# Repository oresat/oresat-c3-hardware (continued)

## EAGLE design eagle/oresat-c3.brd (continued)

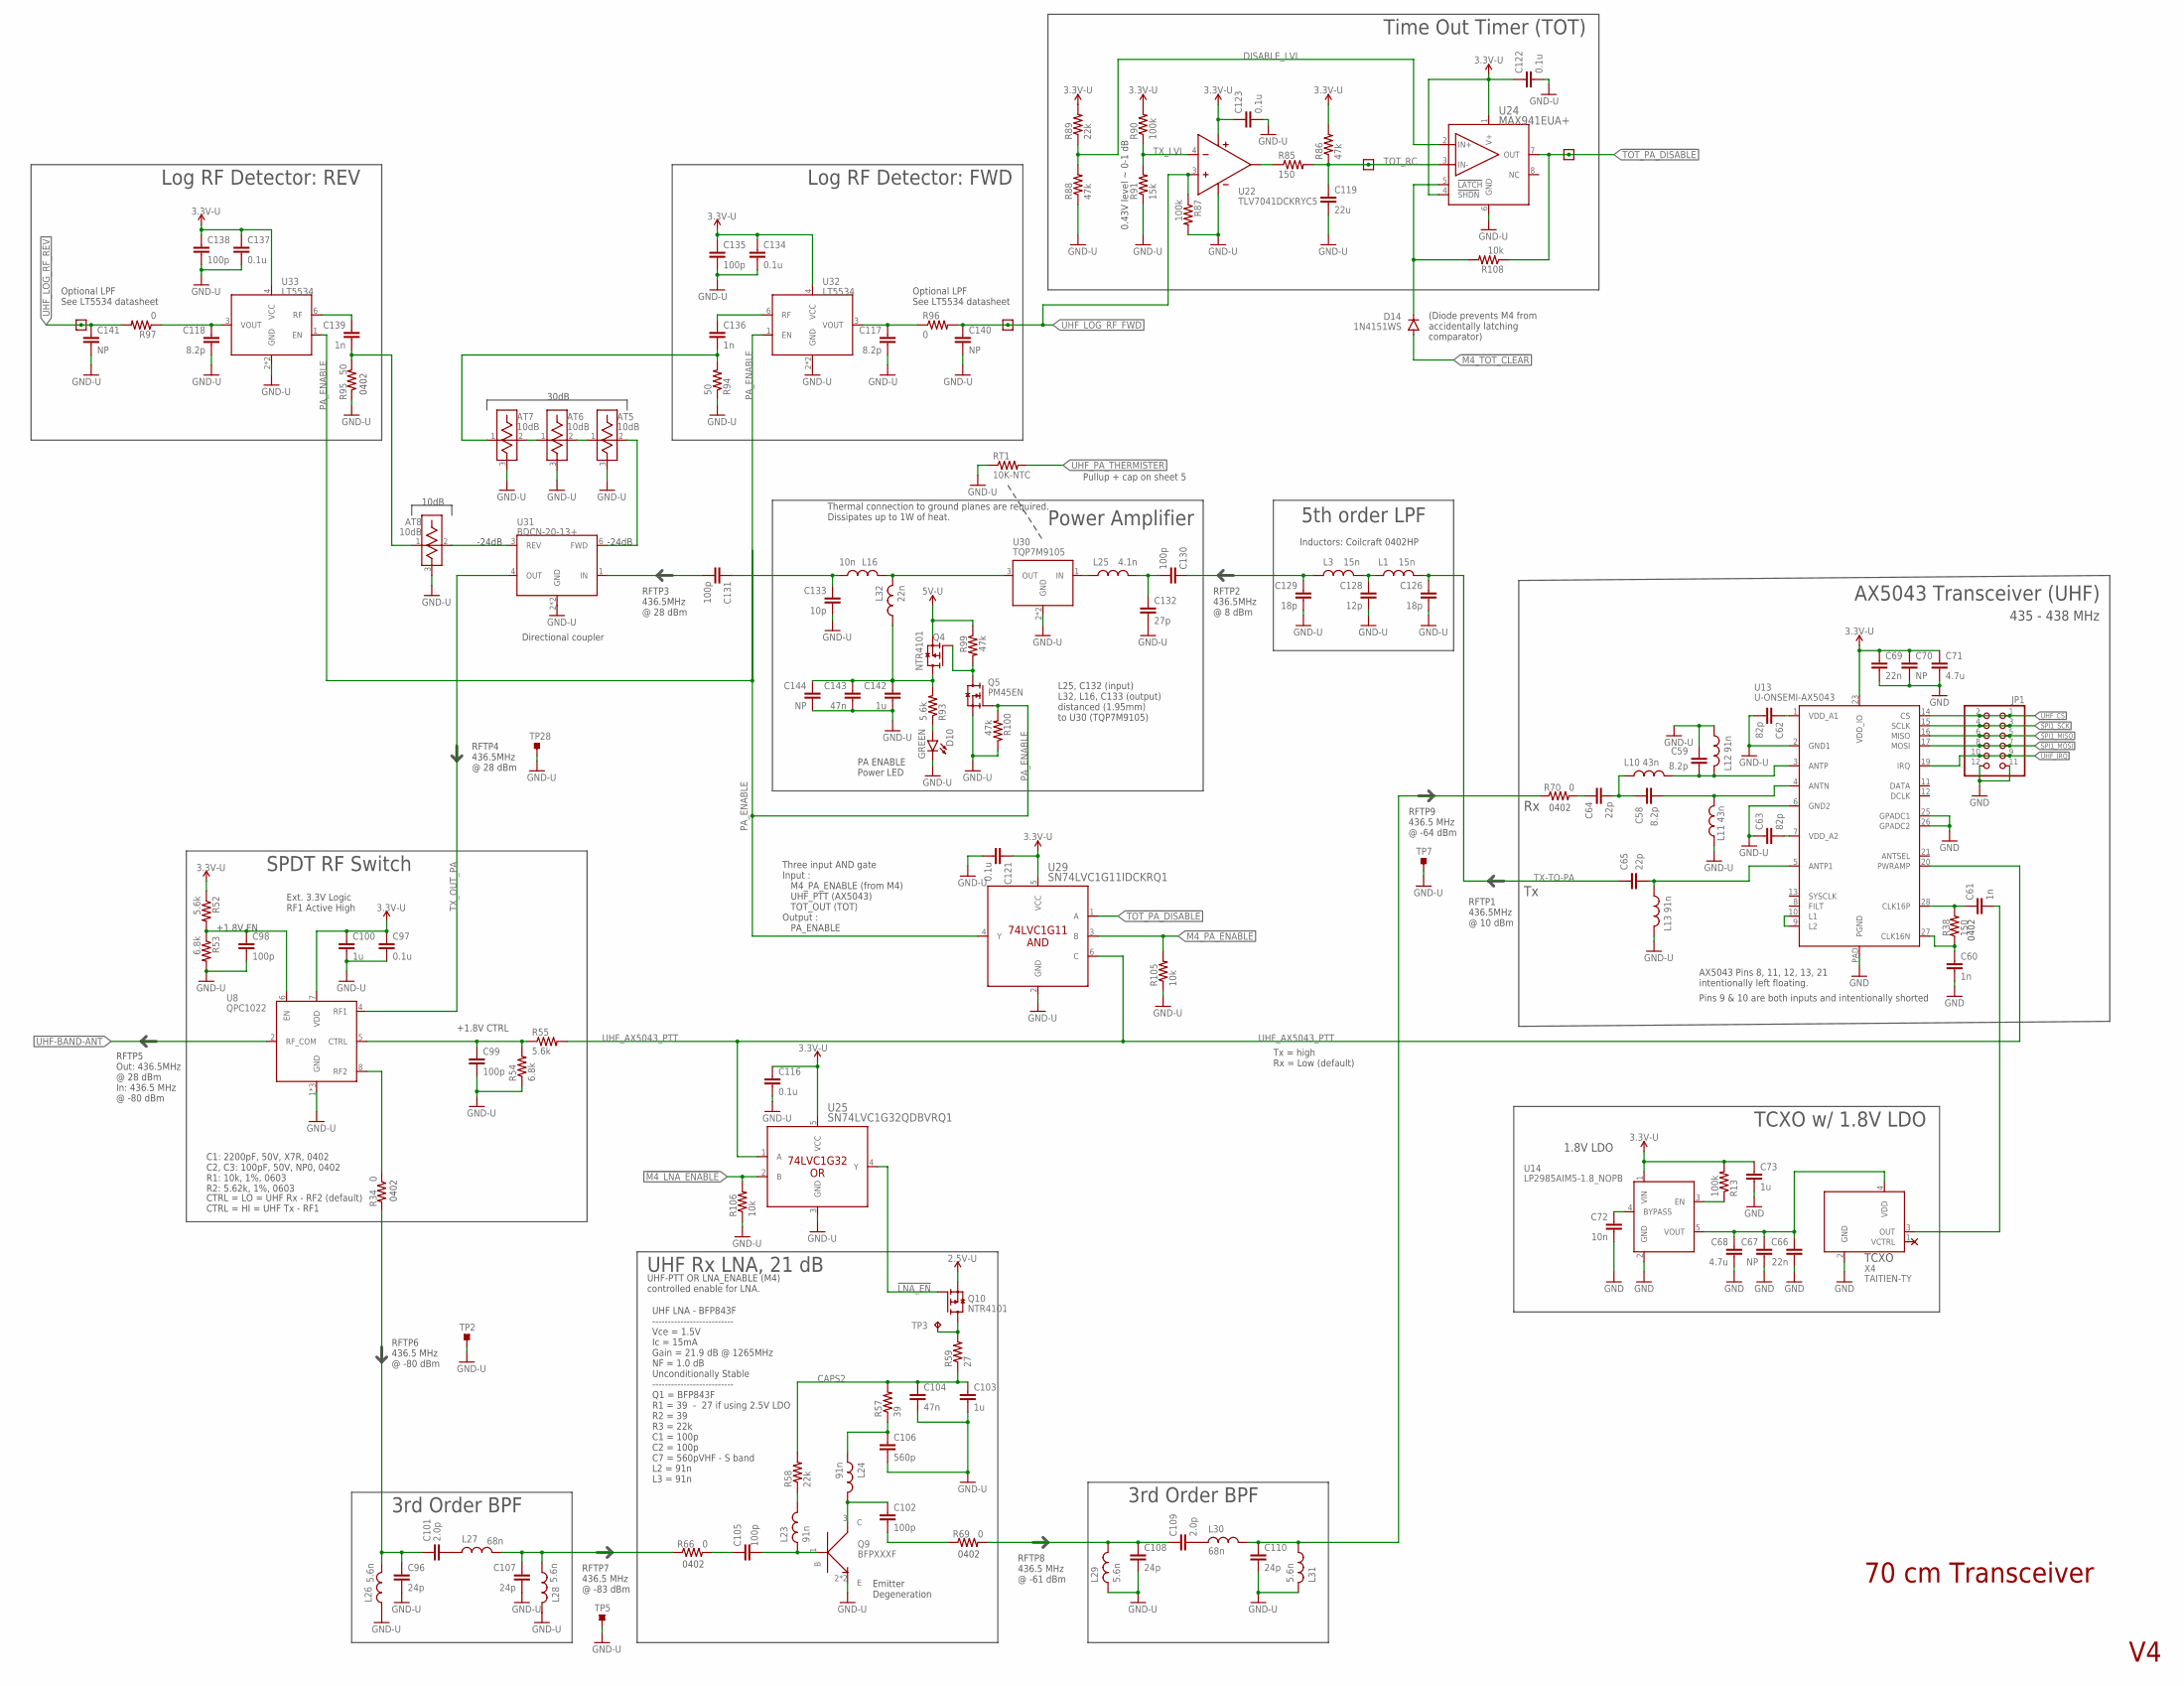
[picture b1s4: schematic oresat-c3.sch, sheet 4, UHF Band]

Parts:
AT5: 10dB; 0805
AT6, AT7, AT8: 10dB; 0603
C58, C59: 8.2p; .0402-C-NOSILK; MANUFACTURER_PART_NUMBER CL05C8R2CB5NNNC; DIGI-KEY_PART_NUMBER 1276-1729-1-ND
C60, C61: 1n; .0402-C-NOSILK; MANUFACTURER_PART_NUMBER CL05C102JB5NNNC; DIGI-KEY_PART_NUMBER 1276-1635-1-ND
C62, C63: 82p; .0402-C-NOSILK; MANUFACTURER_PART_NUMBER CL05C820JB5NNNC; DIGI-KEY_PART_NUMBER 1276-1726-1-ND
C64, C65: 22p; .0402-C-NOSILK; MANUFACTURER_PART_NUMBER CL05C220JB5NNNC; DIGI-KEY_PART_NUMBER 1276-1116-1-ND
C66, C69: 22n; .0603-C-NOSILK; MANUFACTURER_PART_NUMBER CL10B223KA8NNNC; DIGI-KEY_PART_NUMBER 1276-1999-1-ND
C67, C70, C140, C141, C144: NP; .0603-C-NOSILK
C68, C71: 4.7u; .0603-C-NOSILK; MANUFACTURER_PART_NUMBER CL10A475KO8NNNC; DIGI-KEY_PART_NUMBER 1276-1784-1-ND
C72: 10n; .0603-C-NOSILK; MANUFACTURER_PART_NUMBER CL10C103JA8NNNC; DIGI-KEY_PART_NUMBER 1276-2172-1-ND
C73, C100, C103: 1u; .0603-C-NOSILK; MANUFACTURER_PART_NUMBER CC0603KRX5R8BB105; DIGI-KEY_PART_NUMBER 311-1445-1-ND
C96, C107, C108, C110: 24p; .0402-C-NOSILK; MANUFACTURER_PART_NUMBER CL05C240JB5NNNC; DIGI-KEY_PART_NUMBER 1276-1670-1-ND
C97, C116, C121, C122, C123: 0.1u; .0603-C-NOSILK; MANUFACTURER_PART_NUMBER 0603ZD104KAT2A; DIGI-KEY_PART_NUMBER 478-0603ZD104KAT2ACT-ND
C98, C99: 100p; .0603-C-NOSILK; MANUFACTURER_PART_NUMBER 0603ZD104KAT2A; DIGI-KEY_PART_NUMBER 478-0603ZD104KAT2ACT-ND
C101, C109: 2.0p; .0402-C-NOSILK; MANUFACTURER_PART_NUMBER CC0402CRNPO9BN2R0; DIGI-KEY_PART_NUMBER 311-1006-2-ND
C102, C105: 100p; .0402-C-NOSILK; MANUFACTURER_PART_NUMBER CL05C102JB5NNNC; DIGI-KEY_PART_NUMBER 1276-1635-1-ND
C104: 47n; .0603-C-NOSILK; MANUFACTURER_PART_NUMBER CL10B473KB8NNNC; DIGI-KEY_PART_NUMBER 1276-1063-1-ND
C106: 560p; .0402-C-NOSILK; MANUFACTURER_PART_NUMBER CL05C561JB5NNNC; DIGI-KEY_PART_NUMBER 1276-1709-1-ND
C117, C118: 8.2p; .0603-C-NOSILK
C119: 22u; .0603-C-NOSILK
C126, C129: 18p; .0402-C-NOSILK; MANUFACTURER_PART_NUMBER CL05C180JB5NNNC; DIGI-KEY_PART_NUMBER 1276-1140-1-ND
C128: 12p; .0402-C-NOSILK; MANUFACTURER_PART_NUMBER CL05C120JB5NNNC; DIGI-KEY_PART_NUMBER 1276-1178-1-ND
C130: 100p; .0402-C-NOSILK
C131, C135, C138: 100p; .0603-C-NOSILK
C132: 27p; .0402-C-NOSILK
C133: 10p; .0603-C-NOSILK
C134, C137: 0.1u; .0603-C-NOSILK
C136, C139: 1n; .0402-C-NOSILK
C142: 1u; .0603-C-NOSILK
C143: 47n; .0603-C-NOSILK
D10: GREEN; LED-0603
D14: 1N4151WS; SOD323-R
JP1: PINHD-2X6; 2X06; MANUFACTURER_PART_NUMBER 61301221121; DIGI-KEY_PART_NUMBER 732-5297-ND
L1, L3: 15n; .0402-C-NOSILK; MANUFACTURER_PART_NUMBER 0402HP-15NXGLW; DIGI-KEY_PART_NUMBER 2035-1081-1-ND
L10, L11: 43n; .0402-C-NOSILK; MANUFACTURER_PART_NUMBER LQW15AN43NG8ZD; DIGI-KEY_PART_NUMBER 490-15447-1-ND
L12, L13, L23, L24: 91n; .0603-C-NOSILK; MANUFACTURER_PART_NUMBER LQW18AN91NG8ZD; DIGI-KEY_PART_NUMBER 490-15756-1-ND
L16: 10n; .0603-C-NOSILK
L25: 4.1n; .0402-C-NOSILK
L26, L28, L29, L31: 5.6n; .0402-C-NOSILK; MANUFACTURER_PART_NUMBER 0402HP-5N6XGLW; MOUSER_PART_NUMBER 994-0402HP-5N6XGLW
L27, L30: 68n; .0402-C-NOSILK; MANUFACTURER_PART_NUMBER 0402HPH-68NXGLW; MOUSER_PART_NUMBER 994-0402HPH-68NXGLW
L32: 22n; .0805-C-NOSILK
Q4: NTR4101; SOT23-3
Q5: PM45EN; SOT23-3
Q9: BFPXXXF; TSFP4; MANUFACTURER_PART_NUMBER BFP740FH6327XTSA1; DIGI-KEY_PART_NUMBER BFP740FH6327XTSA1CT-ND
Q10: NTR4101; SOT23-3; MANUFACTURER_PART_NUMBER BSS84; DIGI-KEY_PART_NUMBER BSS84CT-ND
R13, R87, R90: 100k; .0603-C-NOSILK
R34, R66, R69, R70: 0; .0402-C-NOSILK; MANUFACTURER_PART_NUMBER RMCF0402ZT0R00; DIGI-KEY_PART_NUMBER RMCF0402ZT0R00CT-ND
R38: 150; .0402-C-NOSILK; MANUFACTURER_PART_NUMBER RT0402BRD07150RL; DIGI-KEY_PART_NUMBER YAG4175CT-ND
R52, R55, R93: 5.6k; .0603-C-NOSILK
R53, R54: 6.8k; .0603-C-NOSILK
R57: 39; .0603-C-NOSILK; MANUFACTURER_PART_NUMBER RMCF0603FT39R0; DIGI-KEY_PART_NUMBER RMCF0603FT39R0CT-ND
R58: 22k; .0603-C-NOSILK; MANUFACTURER_PART_NUMBER ERJ-3EKF2202V; DIGI-KEY_PART_NUMBER P22.0KHCT-ND
R59: 27; .0603-C-NOSILK; MANUFACTURER_PART_NUMBER RMCF0603FT27R0; DIGI-KEY_PART_NUMBER RMCF0603FT27R0CT-ND
R85: 150; .0603-C-NOSILK
R86, R88, R99, R100: 47k; .0603-C-NOSILK
R89: 22k; .0603-C-NOSILK
R91: 15k; .0603-C-NOSILK
R94, R95: 50; .0402-C-NOSILK
R96, R97: 0; .0603-C-NOSILK
R105, R106, R108: 10k; .0603-C-NOSILK
RT1: 10K-NTC; .0603-C-NOSILK
TP1, TP6, TP10, TP29: TEST-POINT-LARGE-SQUARE; 1X01
TP2, TP5, TP7, TP28: TEST-POINT_SMD-SMD-10SN; TESTPOINT_SMD-10SN
TP3: TEST-POINT-LARGE; 1X01
TP4: NO-CONNECTNO-CONNECT-DEVICE; NO-CONNECT-FOOTPRINT
U8: QPC1022; MANUFACTURER_PART_NUMBER QPC1022TR7; MOUSER_PART_NUMBER 772-QPC1022TR7
U13: U-ONSEMI-AX5043; QFN28-5X5-WITH-CENTER-PAD; MANUFACTURER_PART_NUMBER AX5043-1-TW30; DIGI-KEY_PART_NUMBER AX5043-1-TW30OSCT-ND
U14: LP2985AIM5-1.8_NOPB; SOT-23; DIGI-KEY_PART_NUMBER LP2985AIM5-1.8/NOPBCT-ND
U22: TLV7041DCKRYC5; SC70-5
U24: MAX941EUA+; 21-0036K_MXM
U25: SN74LVC1G32QDBVRQ1; DBV5
U29: SN74LVC1G11IDCKRQ1; DCK6
U30: TQP7M9105; U-QORVO-TQP7M9105-PA_TQP7M9105
U31: BDCN-20-13+
U32, U33: LT5534; SC70
X4: TAITIEN-TY; 2.5X2.0; MANUFACTURER_PART_NUMBER TYKTBLSANF-16.000000; DIGI-KEY_PART_NUMBER 1664-1323-1-ND

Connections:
1.8V-U: C66.1, C67.1, C68.1, U14.5 (VOUT), X4.4 (VDD)
2.5V-U: Q10.2 (S); also elsewhere on the board
3.3V-U: C69.1, C70.1, C71.1, C73.1, C97.1, C100.1, C116.1, C121.1, C122.1, C123.1, C134.1, C135.1, C137.1, C138.1, R13.2, R52.1, R86.2, R89.2, R90.2, U8.7 (VDD), U13.23 (VDD_IO), U14.1 (VIN), U22.5 (VCC), U24.1 (V+), U24.4 (!SHDN), U25.5 (VCC), U29.5 (VCC), U32.4 (VCC), U33.4 (VCC); also elsewhere on the board
5V-U: Q4.2 (S), R99.1; also elsewhere on the board
!LATCH_FEEDBACK: D14.C, R108.2, U24.5 (!LATCH)
!LNA_EN: Q10.1 (G), U25.4 (Y)
!M4_LNA_ENABLE: R106.2, U25.2 (B); also elsewhere on the board
!M4_TOT_CLEAR: D14.A; also elsewhere on the board
!TOT_PA_DISABLE: R108.1, TP1.1, U24.7 (OUT), U29.1 (A); also elsewhere on the board
ANTN2: C58.2, L11.2, U13.4 (ANTN)
ANTP4: C59.2, L10.2, L12.1, U13.3 (ANTP)
ANTP5: C65.2, L13.2, U13.5 (ANTP1)
B2: C105.2, L23.1, Q9.1 (B)
C2: C102.1, L24.2, Q9.3 (C)
CAPS2: C103.1, C104.1, R57.2, R58.2, R59.1
CAPS3: C142.1, C143.1, C144.1, L32.2, Q4.3 (D), R93.2
CLKN2: C60.1, R38.1, U13.27 (CLK16N)
CLKP2: C61.1, R38.2, U13.28 (CLK16P)
CTRL1: C99.1, R54.2, R55.1, U8.5 (CTRL)
DISABLE_LVL: R88.2, R89.1, U24.2 (IN+)
EN1: C98.1, R52.2, R53.1, U8.6 (EN)
GND: C60.2, C66.2, C67.2, C68.2, C69.2, C70.2, C71.2, C72.2, C73.2, JP1.11, JP1.12, U13.25 (GPADC1), U13.26 (GPADC2), U13.PAD (PGND), U14.2 (GND), X4.2 (GND); also elsewhere on the board
GND-U: AT5.3 (GND), AT6.3 (GND), AT7.3 (GND), AT8.3 (GND), C59.1, C62.2, C63.1, C96.2, C97.2, C98.2, C99.2, C100.2, C103.2, C104.2, C106.2, C107.2, C108.2, C110.2, C116.2, C117.2, C118.2, C119.2, C121.2, C122.2, C123.2, C126.2, C128.2, C129.2, C132.2, C133.2, C134.2, C135.2, C137.2, C138.2, C140.2, C141.2, C142.2, C143.2, C144.2, D10.C, L11.1, L12.2, L13.1, L26.1, L28.1, L29.1, L31.1, Q5.2 (S), Q9.2 (E), Q9.4 (E), R53.2, R54.1, R87.2, R88.1, R91.1, R94.1, R95.1, R100.1, R105.1, R106.1, RT1.1, TP2.TP, TP5.TP, TP7.TP, TP28.TP, U8.1 (GND), U8.3 (GND), U8.9 (GND), U13.2 (GND1), U13.6 (GND2), U22.2 (VEE), U24.6 (GND), U25.3 (GND), U29.2 (GND), U30.2 (GND), U30.PAD (GND), U31.2 (GND), U31.5 (GND), U32.2 (GND), U32.5 (GND), U33.2 (GND), U33.5 (GND); also elsewhere on the board
M4_PA_ENABLE: R105.2, U29.3 (B); also elsewhere on the board
unnamed: AT5.1, AT6.2
unnamed: C61.2, X4.3 (OUT)
unnamed: C117.1, R96.1, U32.3 (VOUT)
unnamed: U13.9 (L2), U13.10 (L1)
unnamed: C62.1, U13.1 (VDD_A1)
unnamed: C63.2, U13.7 (VDD_A2)
unnamed: C58.1, C64.2, L10.1
unnamed: AT6.1, AT7.2
unnamed: C101.2, L27.1
unnamed: R13.1, U14.3 (EN)
unnamed: L23.2, R58.1
unnamed: C106.1, L24.1, R57.1
unnamed: C72.1, U14.4 (BYPASS)
unnamed: C109.2, L30.1
unnamed: Q10.3 (D), R59.2, TP3.1
unnamed: R34.1, U8.8 (RF2)
unnamed: C105.1, R66.2
unnamed: C102.2, R69.1
unnamed: C64.1, R70.2
unnamed: C118.1, R97.1, U33.3 (VOUT)
unnamed: C128.1, L1.2, L3.1
unnamed: C129.1, C130.1, L3.2
unnamed: R85.1, U22.1 (OUT)
unnamed: C136.1, U32.6 (RF)
unnamed: AT7.1, C136.2, R94.2
unnamed: C139.1, U33.6 (RF)
unnamed: AT8.1, C139.2, R95.2
unnamed: AT5.2, U31.6 (FWD)
unnamed: AT8.2, U31.3 (REV)
unnamed: Q4.1 (G), Q5.3 (D), R99.2
unnamed: D10.A, R93.1
PA_ENABLE: Q5.1 (G), R100.2, U29.4 (Y), U32.1 (EN), U33.1 (EN)
RX2: C110.1, L30.2, L31.2, R70.1
SPI1_MISO: JP1.5, JP1.6, U13.16 (MISO); also elsewhere on the board
SPI1_MOSI: JP1.7, JP1.8, U13.17 (MOSI); also elsewhere on the board
SPI1_SCK: JP1.3, JP1.4, U13.15 (SCLK); also elsewhere on the board
TOT_RC: C119.1, R85.2, R86.1, TP6.1, U24.3 (IN-)
TX-TO-PA: C65.1, C126.1, L1.1
TX-TO-PA$1: C130.2, C132.1, L25.1
TX-TO-PA$2: L25.2, U30.1 (IN)
TX_LVL: R90.1, R91.2, U22.4 (IN-)
TX_OUT: L16.1, L32.1, U30.3 (OUT)
TX_OUT_PA: U8.4 (RF1), U31.4 (OUT)
TX_OUT_PA$1: C131.2, U31.1 (IN)
TX_OUT_PA$2: C131.1, C133.1, L16.2
U-BFP-LNA-RF_IN: C107.1, L27.2, L28.2, R66.1
U-BFP-LNA-RF_OUT: C108.1, C109.1, L29.2, R69.2
UHF-BAND-ANT: U8.2 (RF_COM); also elsewhere on the board
UHF-RX: C96.1, C101.1, L26.2, R34.2
UHF_AX5043_PTT: R55.2, U13.20 (PWRAMP), U25.1 (A), U29.6 (C)
UHF_CS: JP1.1, JP1.2, U13.14 (CS); also elsewhere on the board
UHF_IRQ: JP1.9, JP1.10, U13.19 (IRQ); also elsewhere on the board
UHF_LOG_RF_FWD: C140.1, R87.1, R96.2, TP10.1, U22.3 (IN+); also elsewhere on the board
UHF_LOG_RF_REV: C141.1, R97.2, TP29.1; also elsewhere on the board
UHF_PA_THERMISTER: RT1.2; also elsewhere on the board

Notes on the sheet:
70 cm Transceiver
435 - 438 MHz
AX5043 Pins 8, 11, 12, 13, 21 intentionally left floating.
1.8V LDO
TCXO w/ 1.8V LDO
TCXO
C1: 2200pF, 50V, X7R, 0402 C2, C3: 100pF, 50V, NP0, 0402 R1: 10k, 1%, 0603 R2: 5.62k, 1%, 0603
+1.8V EN
Ext. 3.3V Logic RF1 Active High
+1.8V CTRL
UHF LNA - BFP843F -------------------------- Vce = 1.5V Ic = 15mA Gain = 21.9 dB @ 1265MHz NF = 1.0 dB Unconditionally Stable -------------------------- Q1 = BFP843F R1 = 39 - 27 if using 2.5V LDO R2 = 39 R3 = 22k C1 = 100p C2 = 100p C7 = 560pVHF - S band L2 = 91n L3 = 91n
Emitter Degeneration
3rd Order BPF
AX5043 Transceiver (UHF)
UHF Rx LNA, 21 dB
SPDT RF Switch
CTRL = LO = UHF Rx - RF2 (default) CTRL = HI = UHF Tx - RF1
UHF-PTT OR LNA_ENABLE (M4) controlled enable for LNA.
Pins 9 & 10 are both inputs and intentionally shorted
Power Amplifier
-24dB
Optional LPF See LT5534 datasheet
Thermal connection to ground planes are required. Dissipates up to 1W of heat.
L25, C132 (input) L32, L16, C133 (output) distanced (1.95mm) to U30 (TQP7M9105)
30dB
10dB
Three input AND gate Input : M4_PA_ENABLE (from M4) UHF_PTT (AX5043) TOT_OUT (TOT) Output : PA_ENABLE
PA ENABLE Power LED
(Diode prevents M4 from accidentally latching comparator)
Tx = high Rx = Low (default)
Log RF Detector: FWD
Log RF Detector: REV
Time Out Timer (TOT)
Directional coupler
Pullup + cap on sheet 5
5th order LPF
Inductors: Coilcraft 0402HP
0402
0.43V level ~ 0-1 dB
RFTP1 436.5MHz @ 10 dBm

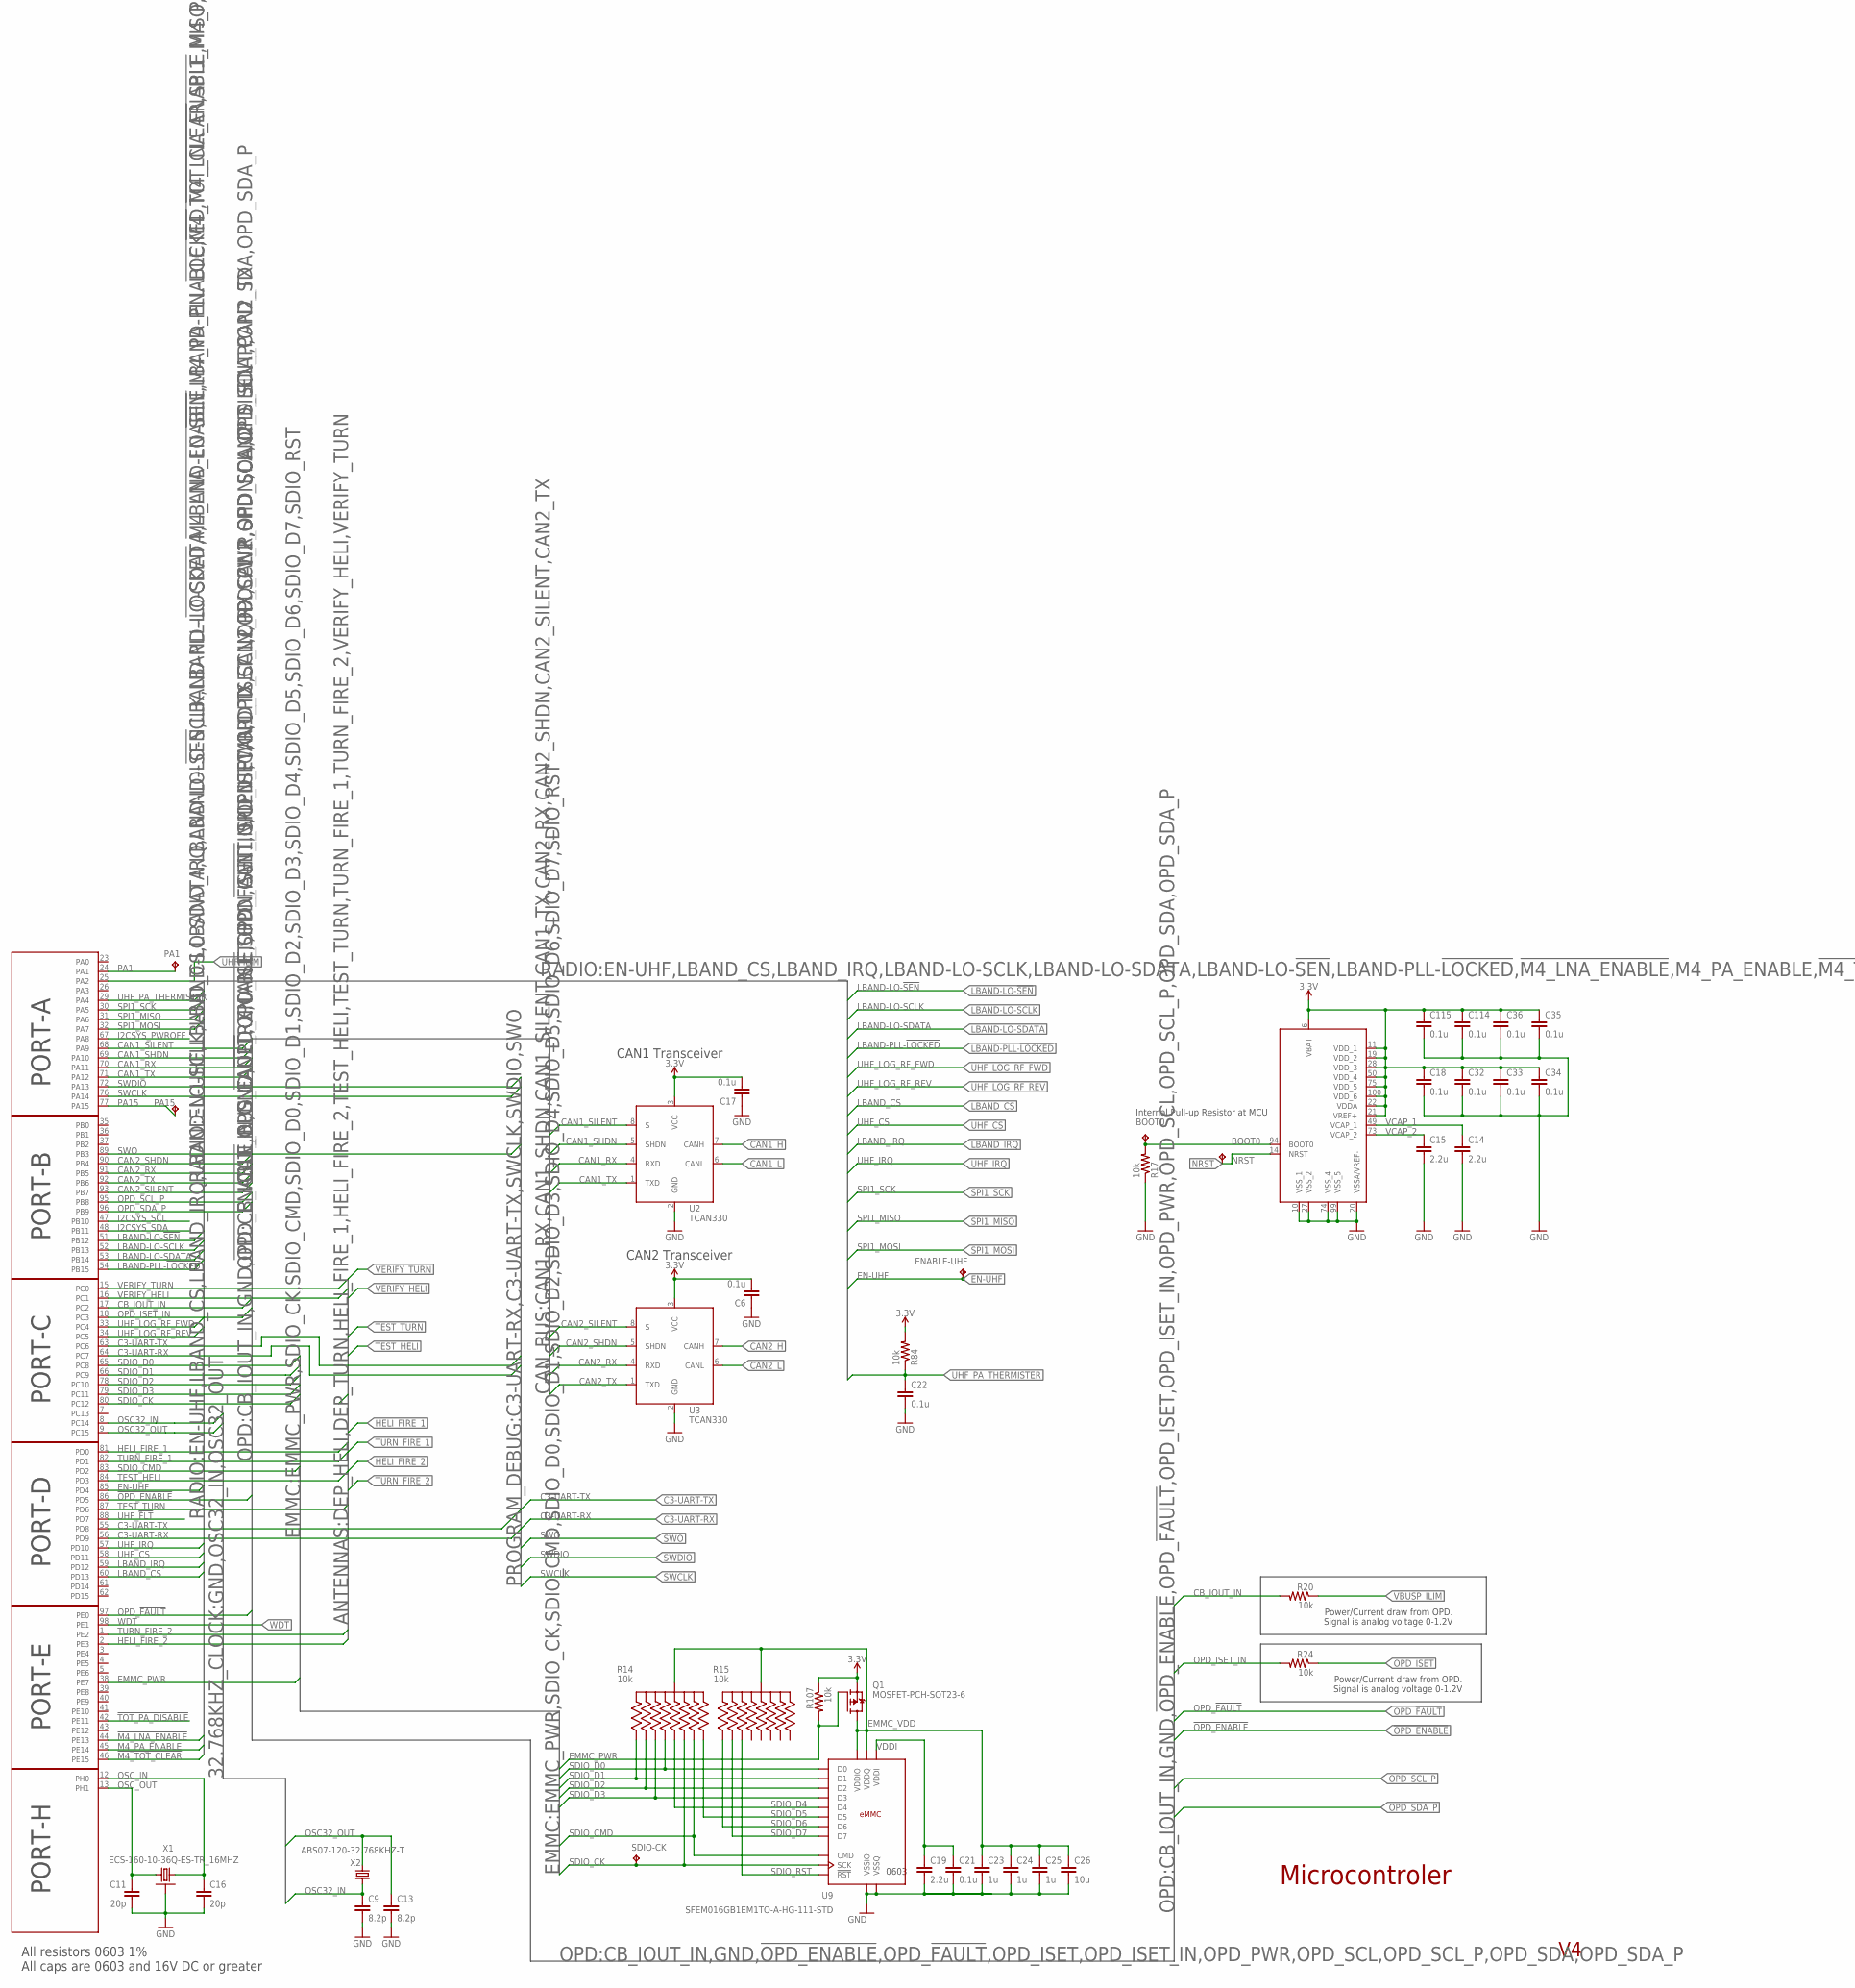
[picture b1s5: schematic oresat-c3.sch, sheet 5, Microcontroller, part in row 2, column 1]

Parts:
BOOT0: TEST-POINT-LARGE; 1X01
C6, C17, C18, C21, C22, C32, C33, C34, C35, C36, C114, C115: 0.1u; .0603-C-NOSILK
C9, C13: 8.2p; .0603-C-NOSILK
C11, C16: 20p; .0603-C-NOSILK
C14, C15, C19: 2.2u; .0603-C-NOSILK
C23, C24, C25: 1u; .0603-C-NOSILK
C26: 10u; .0603-C-NOSILK
ENABLE-UHF: TEST-POINT-LARGE; 1X01
NRST: TEST-POINT-LARGE; 1X01
PA1, PA15: TEST-POINT-LARGE; 1X01
Q1: MOSFET-PCH-SOT23-6; SOT23-6; MANUFACTURER_PART_NUMBER DMP3050LVT-7; DIGI-KEY_PART_NUMBER DMP3050LVT-7DICT-ND
R14, R15: 10k; ARRAY_EXBA-M; DIGI-KEY_PART_NUMBER U7103CT-ND
R17, R20, R24, R84, R107: 10k; .0603-C-NOSILK
SDIO-CK: TEST-POINT-LARGE; 1X01
U2, U3: TCAN330; SOT23-8_TI-DCN; MANUFACTURER_PART_NUMBER TCAN330GDCNT; DIGI-KEY_PART_NUMBER 296-44211-1-ND
U9: SFEM016GB1EM1TO-A-HG-111-STD; BGA-153(11.5X13)(EMMC-BA); MANUFACTURER_PART_NUMBER SFEM016GB1EA1TO-I-GE-111-STD; MOUSER_PART_NUMBER 922-500530
U36: STM32F439VIT6_PORT_BREAKOUT; QFP50P1600X1600X160-100N
X1: ECS-160-10-36Q-ES-TR_16MHZ; 2.5X2.0
X2: ABS07-120-32.768KHZ-T; ABS07-32.768KHZ-T

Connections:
3.3V: C6.2, C17.2, C18.1, C32.1, C33.1, C34.1, C35.1, C36.1, C114.1, C115.1, Q1.4 (S), R84.2, R107.1, U2.3 (VCC), U3.3 (VCC), U36.6 (VBAT), U36.11 (VDD_1), U36.19 (VDD_2), U36.21 (VREF+), U36.22 (VDDA), U36.28 (VDD_3), U36.50 (VDD_4), U36.75 (VDD_5), U36.100 (VDD_6); also elsewhere on the board
!M4_LNA_ENABLE: U36.44 (PE13); also elsewhere on the board
!M4_TOT_CLEAR: U36.46 (PE15); also elsewhere on the board
!OPD_ENABLE: U36.86 (PD5); also elsewhere on the board
!TOT_PA_DISABLE: U36.42 (PE11); also elsewhere on the board
BOOT0: BOOT0.1, R17.2, U36.94 (BOOT0)
C3-UART-RX: U36.56 (PD9), U36.64 (PC7); also elsewhere on the board
C3-UART-TX: U36.55 (PD8), U36.63 (PC6); also elsewhere on the board
CAN1_H: U2.7 (CANH); also elsewhere on the board
CAN1_L: U2.6 (CANL); also elsewhere on the board
CAN1_RX: U2.4 (RXD), U36.70 (PA11)
CAN1_SHDN: U2.5 (SHDN), U36.69 (PA10)
CAN1_SILENT: U2.8 (S), U36.68 (PA9)
CAN1_TX: U2.1 (TXD), U36.71 (PA12)
CAN2_H: U3.7 (CANH); also elsewhere on the board
CAN2_L: U3.6 (CANL); also elsewhere on the board
CAN2_RX: U3.4 (RXD), U36.91 (PB5)
CAN2_SHDN: U3.5 (SHDN), U36.90 (PB4)
CAN2_SILENT: U3.8 (S), U36.93 (PB7)
CAN2_TX: U3.1 (TXD), U36.92 (PB6)
CB_IOUT_IN: R20.2, U36.17 (PC2)
EMMC_PWR: Q1.3 (G), R107.2, U36.38 (PE7)
EMMC_VDD: C23.1, C24.1, C25.1, C26.1, Q1.1 (D), Q1.2 (D), Q1.5 (D), Q1.6 (D), R14.5 (55), R14.10 (55), R15.5 (55), R15.10 (55), U9.C6 (VDDQ), U9.E6 (VDDIO), U9.F5 (VDDIO), U9.J10 (VDDIO), U9.K9 (VDDIO), U9.M4 (VDDQ), U9.N4 (VDDQ), U9.P3 (VDDQ), U9.P5 (VDDQ), U9.P7 (VDDIO)
EN-UHF: ENABLE-UHF.1, U36.85 (PD4); also elsewhere on the board
GND: C6.1, C9.2, C11.2, C13.2, C14.2, C15.2, C16.2, C17.1, C18.2, C19.2, C21.2, C22.2, C23.2, C24.2, C25.2, C26.2, C32.2, C33.2, C34.2, C35.2, C36.2, C114.2, C115.2, R17.1, U2.2 (GND), U3.2 (GND), U9.A6 (VSSIO), U9.C4 (VSSQ), U9.D4 (VSSIO), U9.E7 (VSSIO), U9.G5 (VSSIO), U9.H10 (VSSIO), U9.J5 (VSSIO), U9.K8 (VSSIO), U9.N1 (VSSQ), U9.N2 (VSSQ), U9.N5 (VSSQ), U9.P4 (VSSQ), U9.P6 (VSSQ), U36.10 (VSS_1), U36.20 (VSSA/VREF-), U36.27 (VSS_2), U36.74 (VSS_4), U36.99 (VSS_5), X1.2 (SHIELD), X1.4 (SHIELD); also elsewhere on the board
HELI_FIRE_1: U36.81 (PD0); also elsewhere on the board
HELI_FIRE_2: U36.2 (PE3); also elsewhere on the board
I2CSYS_PWROFF: U36.67 (PA8); also elsewhere on the board
I2CSYS_SCL: U36.47 (PB10); also elsewhere on the board
I2CSYS_SDA: U36.48 (PB11); also elsewhere on the board
LBAND-LO-!SEN: U36.51 (PB12); also elsewhere on the board
LBAND-LO-SCLK: U36.52 (PB13); also elsewhere on the board
LBAND-LO-SDATA: U36.53 (PB14); also elsewhere on the board
LBAND-PLL-!LOCKED: U36.54 (PB15); also elsewhere on the board
LBAND_CS: U36.60 (PD13); also elsewhere on the board
LBAND_IRQ: U36.59 (PD12); also elsewhere on the board
M4_PA_ENABLE: U36.45 (PE14); also elsewhere on the board
NRST: NRST.1, U36.14 (NRST); also elsewhere on the board
OPD_!FAULT: U36.97 (PE0); also elsewhere on the board
OPD_ISET: R24.1; also elsewhere on the board
OPD_ISET_IN: R24.2, U36.18 (PC3)
OPD_SCL_P: U36.95 (PB8); also elsewhere on the board
OPD_SDA_P: U36.96 (PB9); also elsewhere on the board
OSC32_IN: C9.1, U36.8 (PC14), X2.1
OSC32_OUT: C13.1, U36.9 (PC15), X2.2
OSC_IN: C16.1, U36.12 (PH0), X1.1
OSC_OUT: C11.1, U36.13 (PH1), X1.3 (2)
PA1: PA1.1, U36.24 (PA1)
PA15: PA15.1, U36.77 (PA15)
SDIO_CK: R14.7 (77), SDIO-CK.1, U9.M6 (SCK), U36.80 (PC12)
SDIO_CMD: R14.4 (44), U9.M5 (CMD), U36.83 (PD2)
SDIO_D0: R14.8 (88), U9.A3 (D0), U36.65 (PC8)
SDIO_D1: R14.1 (11), U9.A4 (D1), U36.66 (PC9)
SDIO_D2: R14.9 (99), U9.A5 (D2), U36.78 (PC10)
SDIO_D3: R14.2 (22), U9.A1 (D3), U9.B2 (D3), U36.79 (PC11)
SDIO_D4: R14.3 (33), U9.A2 (D4), U9.B3 (D4)
SDIO_D5: R14.6 (66), U9.B4 (D5), U9.C3 (D5), U9.D3 (D5)
SDIO_D6: R15.1 (11), U9.B5 (D6), U9.C5 (D6)
SDIO_D7: R15.9 (99), U9.A7 (D7), U9.B6 (D7)
SDIO_RST: R15.2 (22), U9.K5 (!RST!)
SPI1_MISO: U36.31 (PA6); also elsewhere on the board
SPI1_MOSI: U36.32 (PA7); also elsewhere on the board
SPI1_SCK: U36.30 (PA5); also elsewhere on the board
SWCLK: U36.76 (PA14); also elsewhere on the board
SWDIO: U36.72 (PA13); also elsewhere on the board
SWO: U36.89 (PB3); also elsewhere on the board
TEST_HELI: U36.84 (PD3); also elsewhere on the board
TEST_TURN: U36.87 (PD6); also elsewhere on the board
TURN_FIRE_1: U36.82 (PD1); also elsewhere on the board
TURN_FIRE_2: U36.1 (PE2); also elsewhere on the board
UHF_!FLT: U36.88 (PD7); also elsewhere on the board
UHF_CS: U36.58 (PD11); also elsewhere on the board
UHF_ILIM: U36.25 (PA2); also elsewhere on the board
UHF_IRQ: U36.57 (PD10); also elsewhere on the board
UHF_LOG_RF_FWD: U36.33 (PC4); also elsewhere on the board
UHF_LOG_RF_REV: U36.34 (PC5); also elsewhere on the board
UHF_PA_THERMISTER: C22.1, R84.1, U36.29 (PA4); also elsewhere on the board
VBUSP_ILIM: R20.1; also elsewhere on the board
VCAP_1: C14.1, U36.49 (VCAP_1)
VCAP_2: C15.1, U36.73 (VCAP_2)
VDDI: C19.1, C21.1, U9.C1 (VDDI), U9.C2 (VDDI)
VERIFY_HELI: U36.16 (PC1); also elsewhere on the board
VERIFY_TURN: U36.15 (PC0); also elsewhere on the board
WDT: U36.98 (PE1); also elsewhere on the board

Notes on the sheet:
CAN1 Transceiver
Power/Current draw from OPD.
Signal is analog voltage 0-1.2V
CAN2 Transceiver
Internal Pull-up Resistor at MCU
0603
All resistors 0603 1% All caps are 0603 and 16V DC or greater
Microcontroler

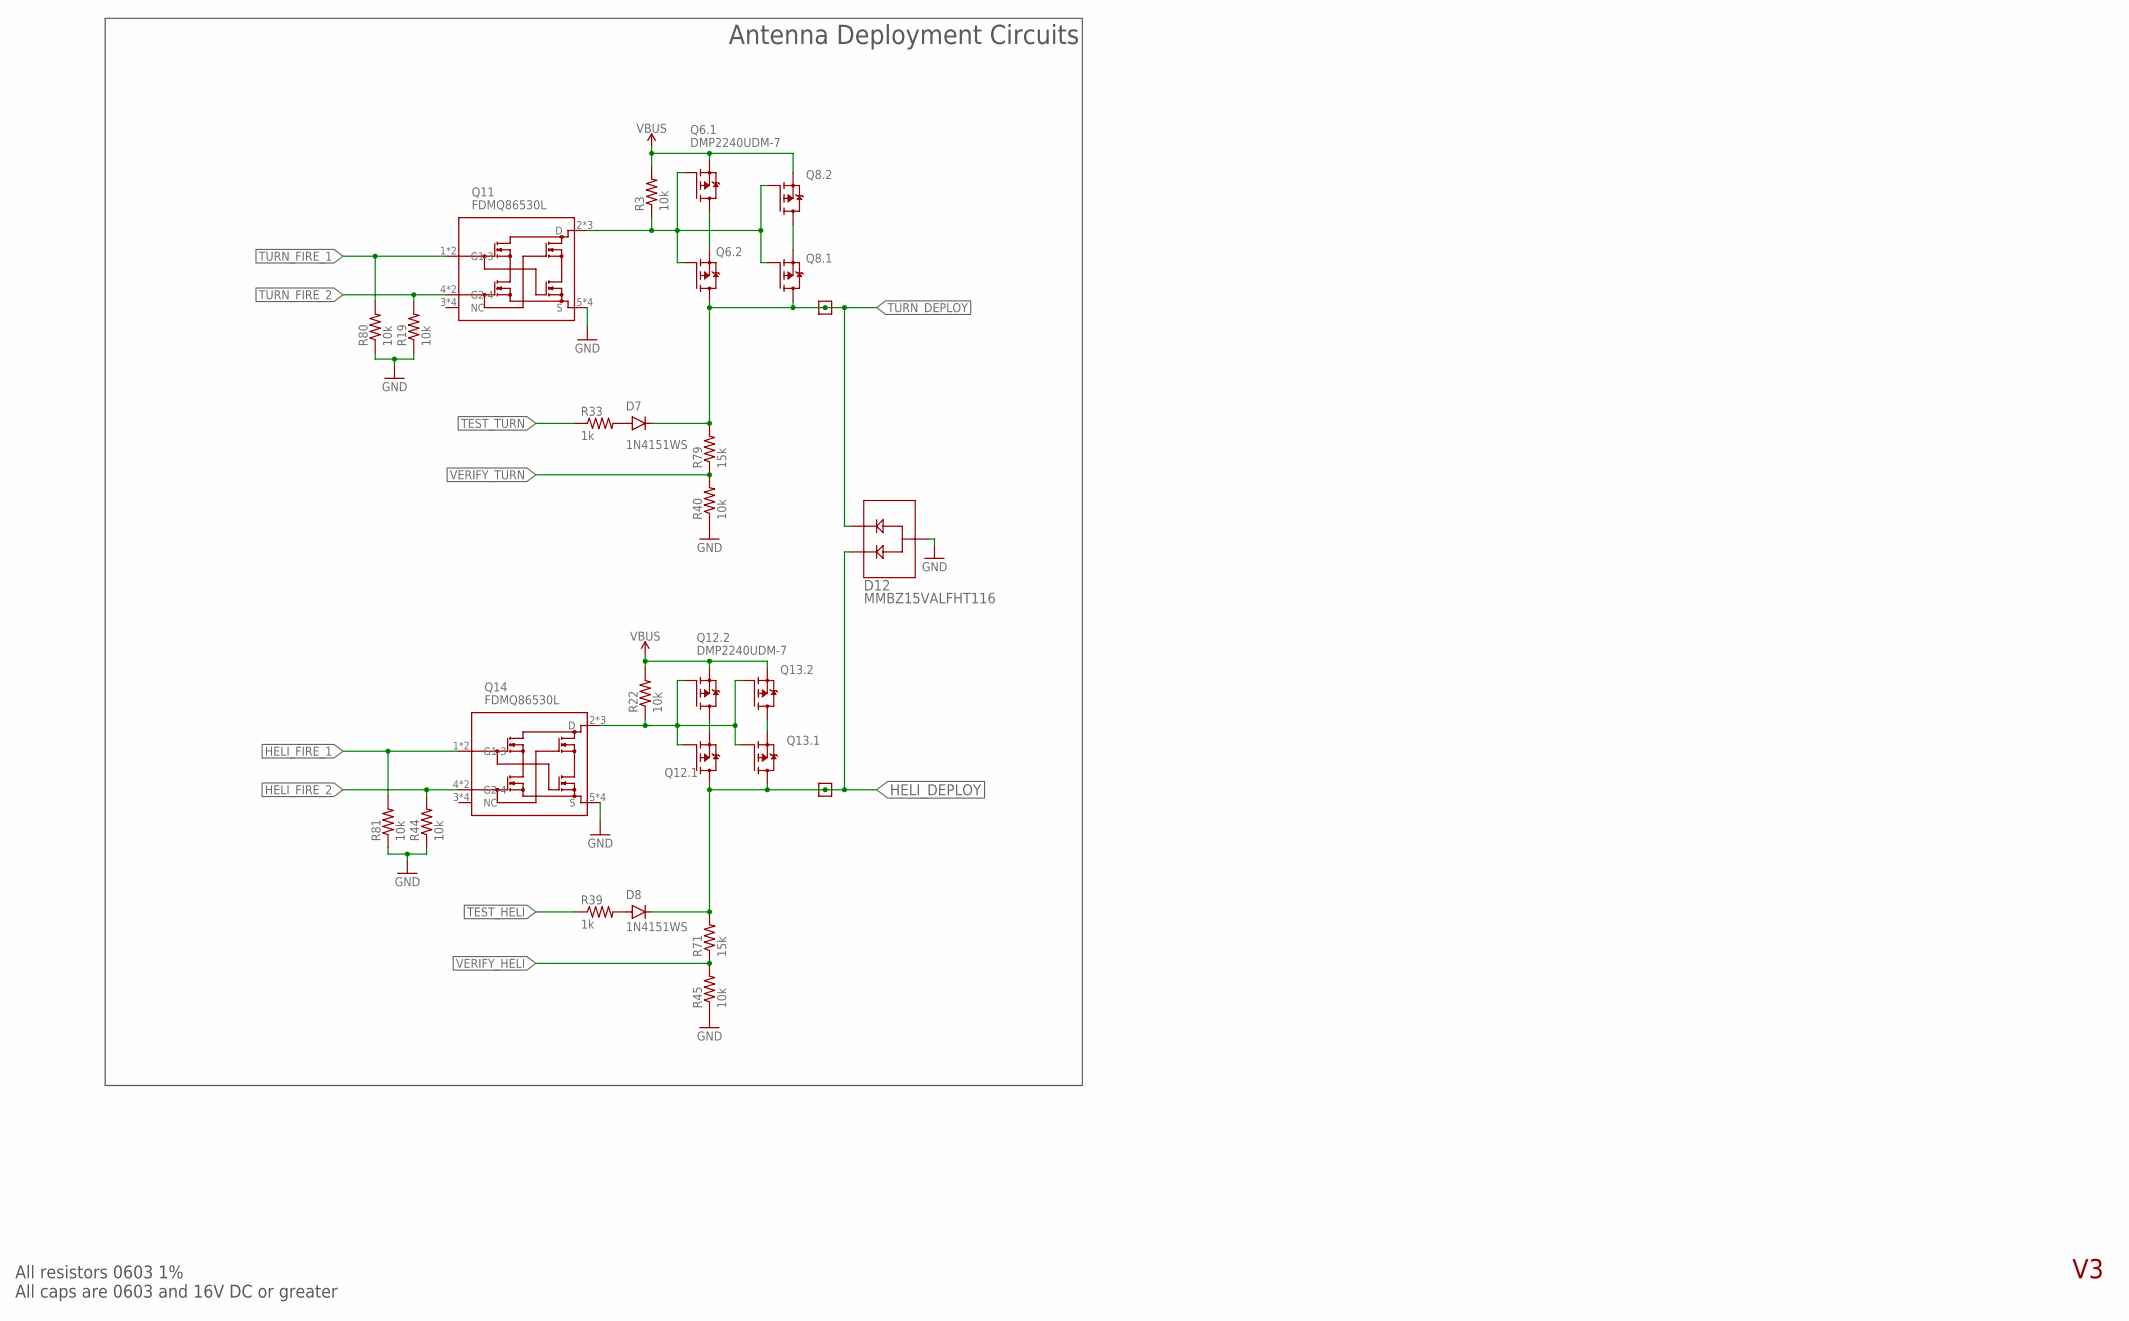
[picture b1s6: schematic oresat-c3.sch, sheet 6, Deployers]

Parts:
D7, D8: 1N4151WS; SOD323-R
D12: MMBZ15VALFHT116; DIO_MMBZ1_ROM
H-DPLY: TEST-POINT-LARGE-SQUARE; 1X01
Q6, Q8, Q12, Q13: DMP2240UDM-7; SOT23-6
Q11, Q14: FDMQ86530L; FDMQ8203
R3, R19, R22, R40, R44, R45, R80, R81: 10k; .0603-C-NOSILK
R33, R39: 1k; .0603-C-NOSILK
R71, R79: 15k; .0603-C-NOSILK
T-DPLY: TEST-POINT-LARGE-SQUARE; 1X01

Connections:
GND: D12.3, Q11.5 (S), Q11.6 (S), Q11.7 (S), Q11.8 (S), Q14.5 (S), Q14.6 (S), Q14.7 (S), Q14.8 (S), R19.1, R40.1, R44.1, R45.1, R80.1, R81.1; also elsewhere on the board
HELI_DEPLOY: D8.C, D12.1, H-DPLY.1, Q12.6 (D), Q13.6 (D), R71.2; also elsewhere on the board
HELI_FIRE_1: Q14.1 (G1-3), Q14.9 (G1-3), R81.2; also elsewhere on the board
HELI_FIRE_2: Q14.4 (G2-4), Q14.12 (G2-4), R44.2; also elsewhere on the board
HELI_NMOS_DRAIN: Q12.1 (G), Q12.3 (G), Q13.1 (G), Q13.3 (G), Q14.2 (D), Q14.11 (D), Q14.13 (D), R22.1
unnamed: Q6.4 (D), Q6.5 (S)
unnamed: Q8.4 (D), Q8.5 (S)
unnamed: D7.A, R33.2
unnamed: Q13.4 (D), Q13.5 (S)
unnamed: D8.A, R39.2
unnamed: Q12.4 (D), Q12.5 (S)
TEST_HELI: R39.1; also elsewhere on the board
TEST_TURN: R33.1; also elsewhere on the board
TURN_DEPLOY: D7.C, D12.2, Q6.6 (D), Q8.6 (D), R79.2, T-DPLY.1; also elsewhere on the board
TURN_FIRE_1: Q11.1 (G1-3), Q11.9 (G1-3), R80.2; also elsewhere on the board
TURN_FIRE_2: Q11.4 (G2-4), Q11.12 (G2-4), R19.2; also elsewhere on the board
TURN_NMOS_DRAIN: Q6.1 (G), Q6.3 (G), Q8.1 (G), Q8.3 (G), Q11.2 (D), Q11.11 (D), Q11.13 (D), R3.1
VBUS: Q6.2 (S), Q8.2 (S), Q12.2 (S), Q13.2 (S), R3.2, R22.2; also elsewhere on the board
VERIFY_HELI: R45.2, R71.1; also elsewhere on the board
VERIFY_TURN: R40.2, R79.1; also elsewhere on the board

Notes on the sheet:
All resistors 0603 1% All caps are 0603 and 16V DC or greater
Antenna Deployment Circuits
